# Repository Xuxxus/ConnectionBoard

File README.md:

# ConnectionBoard
PCB to connect general Hardware
# First board
Considerations:
-> 13 IMUs, all connected to Host (ADO, SCL and SDA)
-> 1 INT (interrupt) Pin considered
-> 2 LEDS connected

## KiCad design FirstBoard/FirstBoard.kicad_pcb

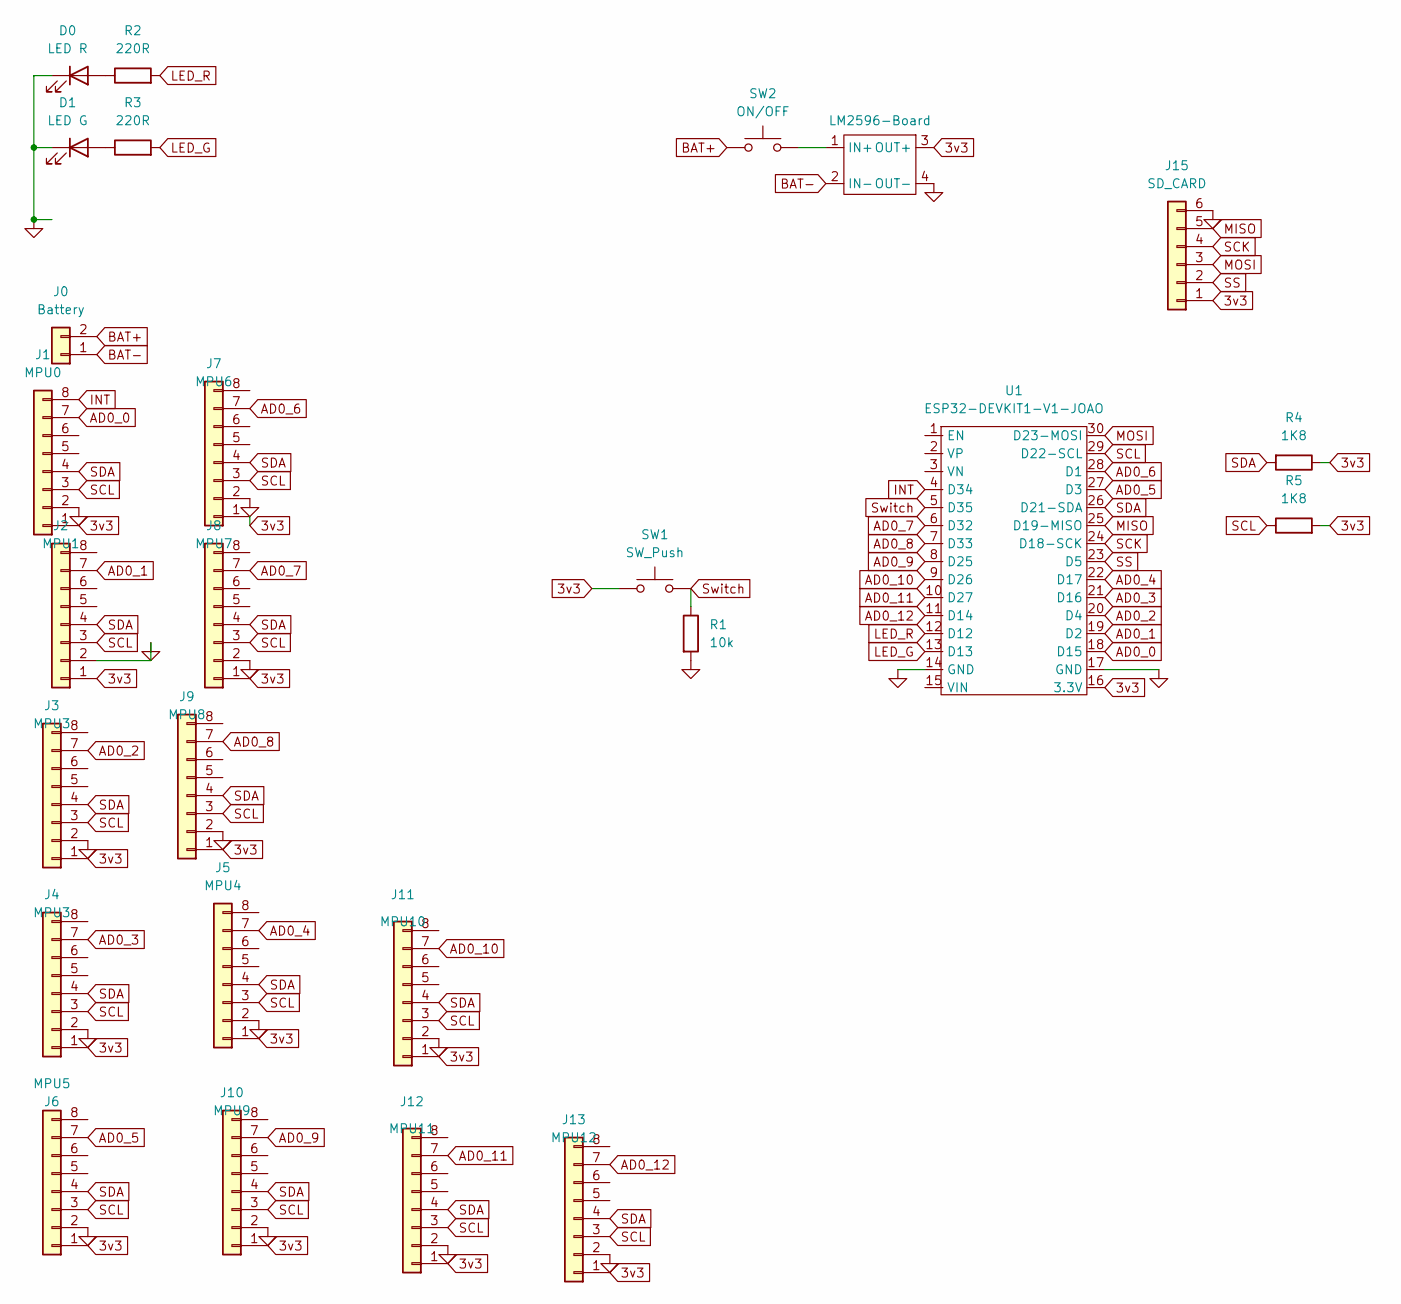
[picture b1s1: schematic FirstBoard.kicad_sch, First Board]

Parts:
D0: LED R; R_Axial_DIN0204_L3.6mm_D1.6mm_P7.62mm_Horizontal
D1: LED G; R_Axial_DIN0204_L3.6mm_D1.6mm_P7.62mm_Horizontal
J0: Battery; PinHeader_1x02_P2.54mm_Vertical
J1: MPU0; PinHeader_1x08_P2.54mm_Vertical
J2: MPU1; PinHeader_1x08_P2.54mm_Vertical
J3, J4: MPU3; PinHeader_1x08_P2.54mm_Vertical
J5: MPU4; PinHeader_1x08_P2.54mm_Vertical
J6: MPU5; PinHeader_1x08_P2.54mm_Vertical
J7: MPU6; PinHeader_1x08_P2.54mm_Vertical
J8: MPU7; PinHeader_1x08_P2.54mm_Vertical
J9: MPU8; PinHeader_1x08_P2.54mm_Vertical
J10: MPU9; PinHeader_1x08_P2.54mm_Vertical
J11: MPU10; PinHeader_1x08_P2.54mm_Vertical
J12: MPU11; PinHeader_1x08_P2.54mm_Vertical
J13: MPU12; PinHeader_1x08_P2.54mm_Vertical
J15: SD_CARD; PinHeader_1x06_P2.54mm_Vertical
R1: 10k; R_Axial_DIN0207_L6.3mm_D2.5mm_P10.16mm_Horizontal
R2, R3: 220R; R_Axial_DIN0207_L6.3mm_D2.5mm_P10.16mm_Horizontal
R4, R5: 1K8; R_Axial_DIN0207_L6.3mm_D2.5mm_P10.16mm_Horizontal
SW1: SW_Push; SW_PUSH_6mm_H5mm
SW2: ON/OFF; BOTAO-ONOFF
U1: ESP32-DEVKIT1-V1-JOAO; MODULE_ESP32_DEVKIT_V1
U2: LM2596-Board; LM2596_Board

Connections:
3v3: J1.1, J2.1, J3.1, J4.1, J5.1, J6.1, J7.1, J8.1, J9.1, J10.1, J11.1, J12.1, J13.1, J15.1, R4.1, R5.2, SW1.1, U1.16 (3.3V), U2.3 (OUT+)
AD0_0: J1.7, U1.18 (D15)
AD0_1: J2.7, U1.19 (D2)
AD0_2: J3.7, U1.20 (D4)
AD0_3: J4.7, U1.21 (D16)
AD0_4: J5.7, U1.22 (D17)
AD0_5: J6.7, U1.27 (D3)
AD0_6: J7.7, U1.28 (D1)
AD0_7: J8.7, U1.6 (D32)
AD0_8: J9.7, U1.7 (D33)
AD0_9: J10.7, U1.8 (D25)
AD0_10: J11.7, U1.9 (D26)
AD0_11: J12.7, U1.10 (D27)
AD0_12: J13.7, U1.11 (D14)
BAT+: J0.2, SW2.1
BAT-: J0.1, U2.2 (IN-)
GND: D0.1 (K), D1.1 (K), J1.2, J2.2, J3.2, J4.2, J5.2, J6.2, J7.2, J8.2, J9.2, J10.2, J11.2, J12.2, J13.2, J15.6, R1.2, U1.14 (GND), U1.17 (GND), U2.4 (OUT-)
INT: J1.8, U1.4 (D34)
LED_G: R3.2, U1.13 (D13)
LED_R: R2.2, U1.12 (D12)
MISO: J15.5, U1.25 (D19-MISO)
MOSI: J15.3, U1.30 (D23-MOSI)
unnamed: D0.2 (A), R2.1
unnamed: D1.2 (A), R3.1
unnamed: SW2.2, U2.1 (IN+)
SCK: J15.4, U1.24 (D18-SCK)
SCL: J1.3, J2.3, J3.3, J4.3, J5.3, J6.3, J7.3, J8.3, J9.3, J10.3, J11.3, J12.3, J13.3, R5.1, U1.29 (D22-SCL)
SDA: J1.4, J2.4, J3.4, J4.4, J5.4, J6.4, J7.4, J8.4, J9.4, J10.4, J11.4, J12.4, J13.4, R4.2, U1.26 (D21-SDA)
SS: J15.2, U1.23 (D5)
Switch: R1.1, SW1.2, U1.5 (D35)

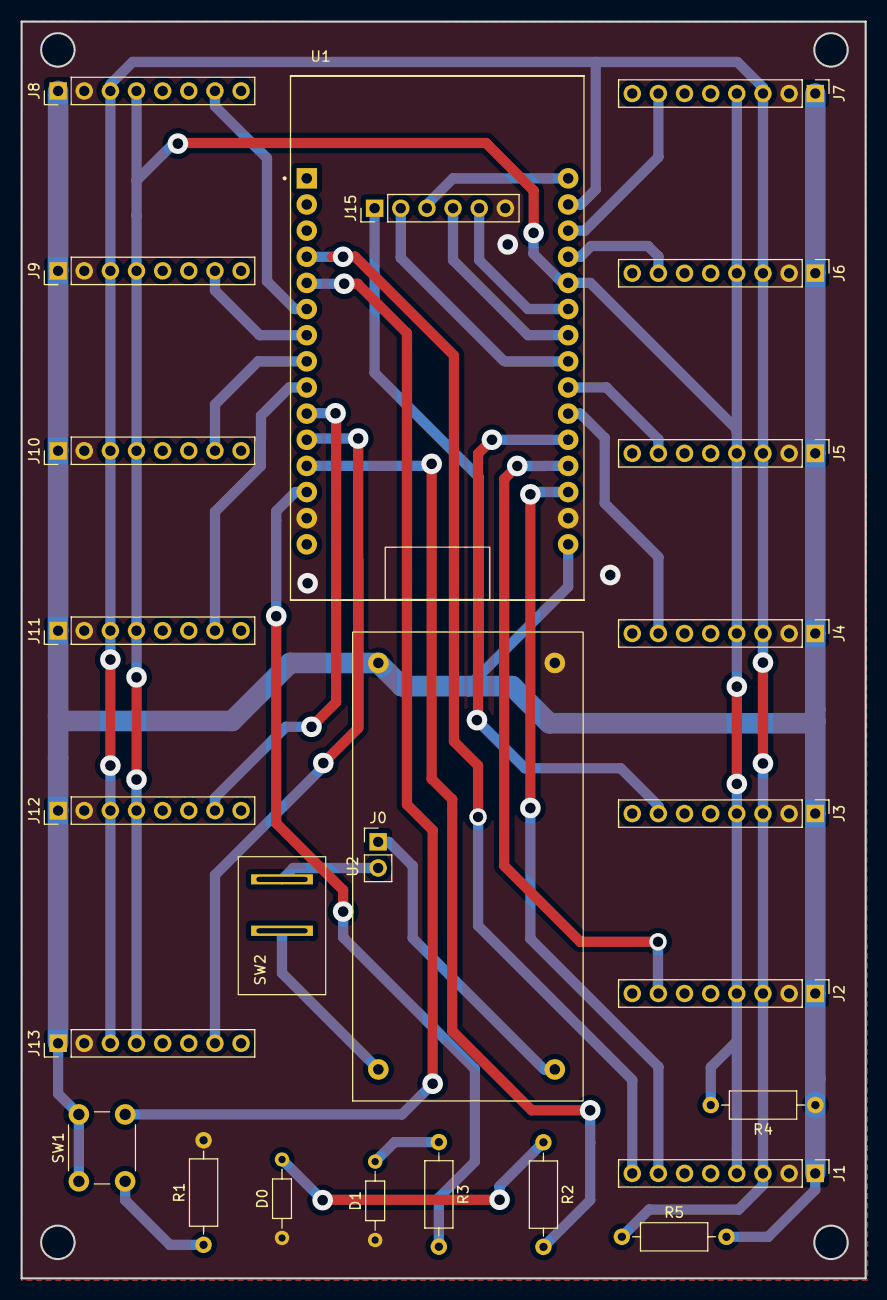
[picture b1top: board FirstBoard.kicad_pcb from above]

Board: 2 copper layers, 82.0 x 122.1 mm, 26 parts (0 on the bottom side), 30 nets.

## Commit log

2023-07-02 First commit-No PCB
2023-07-02 Adding symbols, footprint and first pcb drawing
2023-08-16 changing layour, adding SD card
2023-08-19 First version -SD Card+13 IMUs
2023-08-22 Bigger space and vias
2023-08-22 Deleted pdf
2023-08-22 changing number of pins on MPU connector
2023-08-23 ending the first PCB done-v1
2023-10-13 TODO develop lines and put footprints
2023-10-13 idk some changes
2023-10-15 Finished V2
2023-10-17 Few pins adjusted
2023-10-17 bigger space between ESP and Source
2023-10-17 Adjusted holes
2023-10-18 Holes and better space arrangement
2023-10-23 Input-only pin changed
2023-10-24 Adding gerber files
